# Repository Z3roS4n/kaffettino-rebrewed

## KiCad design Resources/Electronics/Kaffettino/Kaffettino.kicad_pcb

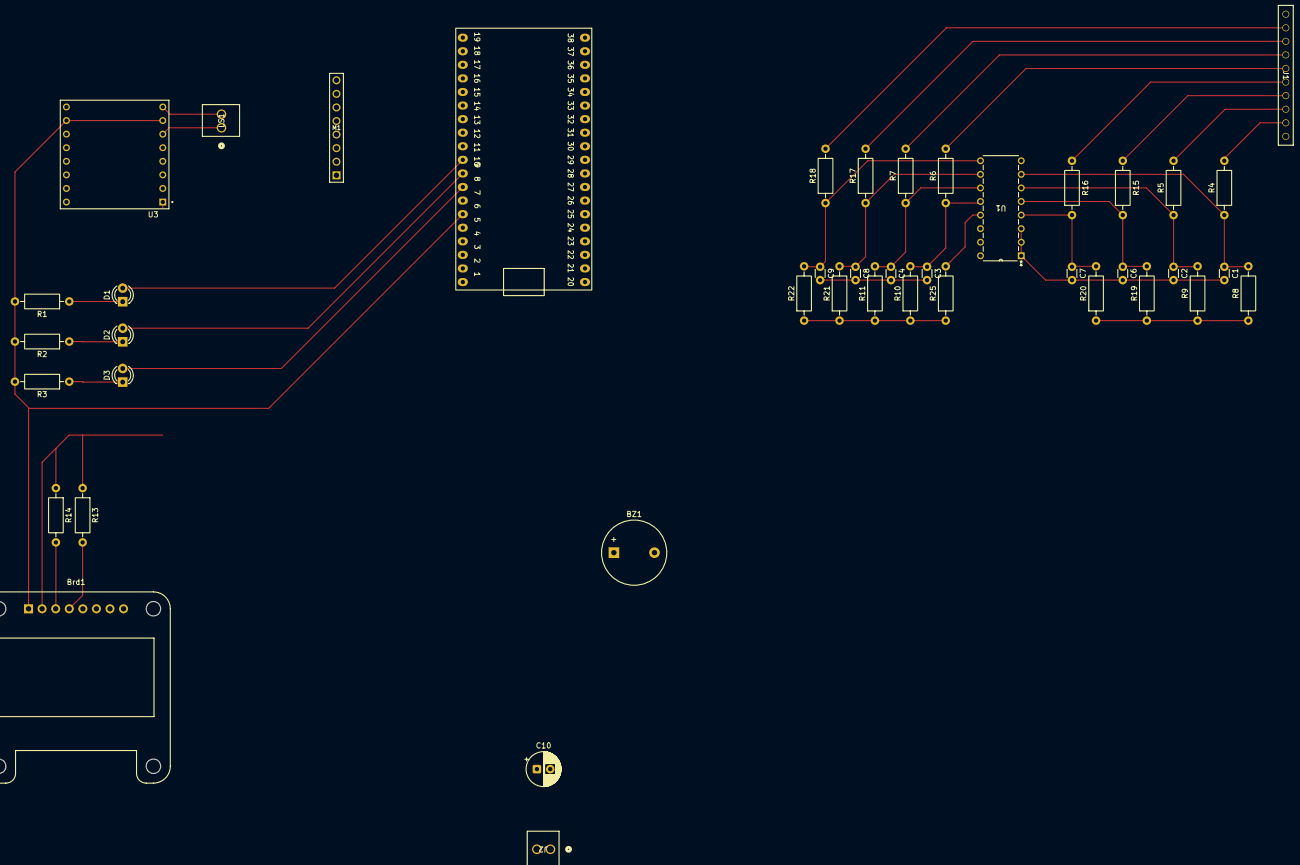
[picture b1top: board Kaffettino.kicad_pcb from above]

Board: 2 copper layers, 43 parts (0 on the bottom side), 38 nets.

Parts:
BZ1: Buzzer; Buzzer_12x9.5RM7.6
Brd1: SSD1306; Adafruit_SSD1306
C1, C2, C3, C4, C6, C7, C8, C9: 100nF; C_Disc_D3.0mm_W1.6mm_P2.50mm
C10: 4.7uF; CP_Radial_D6.3mm_P2.50mm
D1: Green; LED_D3.0mm
D2: Yellow; LED_D3.0mm
D3: Red; LED_D3.0mm
J1: PPTC101LFBN-RC; CONN10_101LFBN-RC_SUL
J2: OSTVN02A150; CONN_OSTVN02A150_OST
LS1: Speaker; CONN_OSTVN02A150_OST
M1: RFID-RC522
R1, R2, R3: 330; R_Axial_DIN0207_L6.3mm_D2.5mm_P10.16mm_Horizontal
R4, R5, R6, R7, R13, R14, R15, R16, R17, R18, R25: 1k; R_Axial_DIN0207_L6.3mm_D2.5mm_P10.16mm_Horizontal
R8, R9, R10, R11, R19, R20, R21, R22: 10k; R_Axial_DIN0207_L6.3mm_D2.5mm_P10.16mm_Horizontal
U1: PCF8574AN; N16
U2: ESP32-38Pin-Wroom; ESP32_38pin
U3: DFR0299; MODULE_DFR0299

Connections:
+3.3V: Brd1.2 (VCC), M1.8 (3V3), R8.1, R9.1, R10.1, R11.1, R13.1, R14.1, R19.1, R20.1, R21.1, R22.1, R25.1, U1.16 (VCC), U2.19 (3.3v), U3.1 (VCC)
+5V: C10.1, J2.2, U2.1 (5v)
/BUZZER: BZ1.1 (+), U2.27 (GPIO16)
/GEN_SCL: Brd1.3 (SCL), R14.2, U1.14 (SCL), U2.36 (GPIO22)
/GEN_SDA: Brd1.4 (SDA), R13.2, U1.15 (SDA), U2.33 (GPIO21)
/GREEN: D1.2 (A), U2.10 (GPIO26)
/KP_C1: C9.1, R18.1, R22.2, U1.9 (P4)
/KP_C2: C8.1, R17.1, R21.2, U1.10 (P5)
/KP_C3: C4.1, R7.1, R11.2, U1.11 (P6)
/KP_C4: C3.1, R6.1, R10.2, U1.12 (P7)
/KP_R1: C7.1, R16.1, R20.2, U1.4 (P0)
/KP_R2: C6.1, R15.1, R19.2, U1.5 (P1)
/KP_R3: C2.1, R5.1, R9.2, U1.6 (P2)
/KP_R4: C1.1, R4.1, R8.2, U1.7 (P3)
/MICRO_SD_RX: U2.12 (GPIO33), U3.2 (RX)
/MICRO_SD_TX: U2.13 (GPIO32), U3.3 (TX)
/RED: D3.2 (A), U2.8 (GPIO14)
/RFID_MISO: M1.4 (MISO), U2.31 (GPIO19)
/RFID_MOSI: M1.3 (MOSI), U2.37 (GPIO23)
/RFID_RST: M1.7 (RST), U2.15 (GPIO34)
/RFID_SCK: M1.2 (SCK), U2.30 (GPIO18)
/RFID_SDA: M1.1 (SDA), U2.26 (GPIO4)
/YELLOW: D2.2 (A), U2.9 (GPIO27)
GNDREF: BZ1.2 (-), Brd1.1 (GND), C1.2, C2.2, C3.2, C4.2, C6.2, C7.2, C8.2, C9.2, C10.2, J2.1, M1.6 (GND), R1.2, R2.2, R3.2, U1.1 (A0), U1.2 (A1), U1.3 (A2), U1.8 (GND), U2.6 (GND), U2.32 (GND), U2.38 (GND), U3.7 (GND), U3.10 (GND)
unnamed: D1.1 (K), R1.1
unnamed: D2.1 (K), R2.1
unnamed: D3.1 (K), R3.1
unnamed: J1.2, R18.2
unnamed: J1.3, R17.2
unnamed: J1.4, R7.2
unnamed: J1.5, R6.2
unnamed: J1.6, R16.2
unnamed: J1.7, R15.2
unnamed: J1.8, R5.2
unnamed: J1.9, R4.2
unnamed: R25.2, U1.13 (*INT)
unnamed: LS1.1, U3.6 (SPK1)
unnamed: LS1.2, U3.8 (SPK2)

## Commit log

2025-10-30 Create LICENSE
2025-10-30 Project Initiated with images
2025-10-30 Initialized arduino code
2025-10-31 Started working on electrical schema
2025-11-04 GramIO Configuration
2025-11-05 PCB Design - continuing schema
2025-11-08 Initialize backend API structure and config files
    Added initial setup for the backend API in Code/backend/api, including .gitignore, package.json, tsconfig.json, and dependencies for Fastify and TypeScript. Removed the old API entry point at Code/Ba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
2025-11-09 Add Prisma, authentication, and initial API setup
    Introduces Prisma ORM with schema and generated client, adds authentication and CORS plugins, and sets up initial Fastify API routes and server structure. Updates dependencies to include Prisma, auth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
2025-11-10 Refactor API structure and improve route loading
    Replaces the Fastify plugin-based route and auth loading with autoload for modular route registration. Moves authentication logic to a new src/auth.ts file, removes the old auth and index route plugi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
2025-11-11 Finished electrical schema and removed node_modules
2025-11-12 Add initial Prisma schema and generated client
    Introduced a comprehensive Prisma schema with models for User, Session, Account, Verification, UserData, TopUp, Transaction, Wallet, Card, Product, Inventory, and Auletta, including relationships and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
2025-11-12 Add BetterAuth integration and update TypeScript config
    Introduced a new Fastify plugin for BetterAuth authentication and registered it in the server setup. Updated import paths to use .js extensions for compatibility, adjusted Prisma generator provider, 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
2025-11-13 Added expansion pins and changed power method in electrical schema
2025-11-13 Refactor auth integration and improve server setup
    Refactored authentication to use default export and updated type exports. Simplified Fastify auth plugin registration and improved CORS configuration for better security and flexibility. Enhanced ser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
2025-11-14 Add protected route and session decorator for API
    Introduced a new protected API route under /api/v1/protected that requires user authentication. Added a session decorator utility and an authentication hook to manage session state in Fastify request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
2025-11-14 Update Prisma schema and API docs for new models and fields
    Refactored the Prisma schema: added Auletta and Product_Inventory models, updated relationships between Product and Inventory, and introduced new fields (description, discount) to TopUp and Transacti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
2025-11-14 Add user and wallet API route scaffolding and update docs
    Expanded API documentation in routes.md with detailed endpoint specifications, data models, and permissions. Added initial user route handler in src/routes/api/v1/user.ts to return authenticated user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
2025-11-14 Refactor API: remove wallet, add handlers, cleanup
    Removed wallet route and related decorator and hook files. Introduced new utility handlers for user and wallet logic, and added a log method decorator. Updated user route and server setup to use new 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
2025-11-14 Add user update endpoint and error handler utility
    Introduces a POST /user endpoint to update user data, with support for updating aulettaId, role, and birthDate. Adds a reusable error handler utility for standardized error responses. Enhances loggin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
2025-11-15 Add session and permissions middleware, inventory route
    Introduces session and permissions middleware for Fastify, decorates requests with session data, and adds type definitions for session on FastifyRequest. Adds a new inventory route with role-based ac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
2025-11-15 Add user role management and permissions handling
    Introduces a new permissions-handler utility for role hierarchy and validation, and adds endpoints for updating user roles with proper permission checks. Refactors user-handler to separate role updat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
